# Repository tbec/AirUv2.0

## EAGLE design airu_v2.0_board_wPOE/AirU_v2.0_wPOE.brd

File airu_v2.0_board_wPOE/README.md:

# AirUv2.0 Schematic and Layout

Last Modified: …

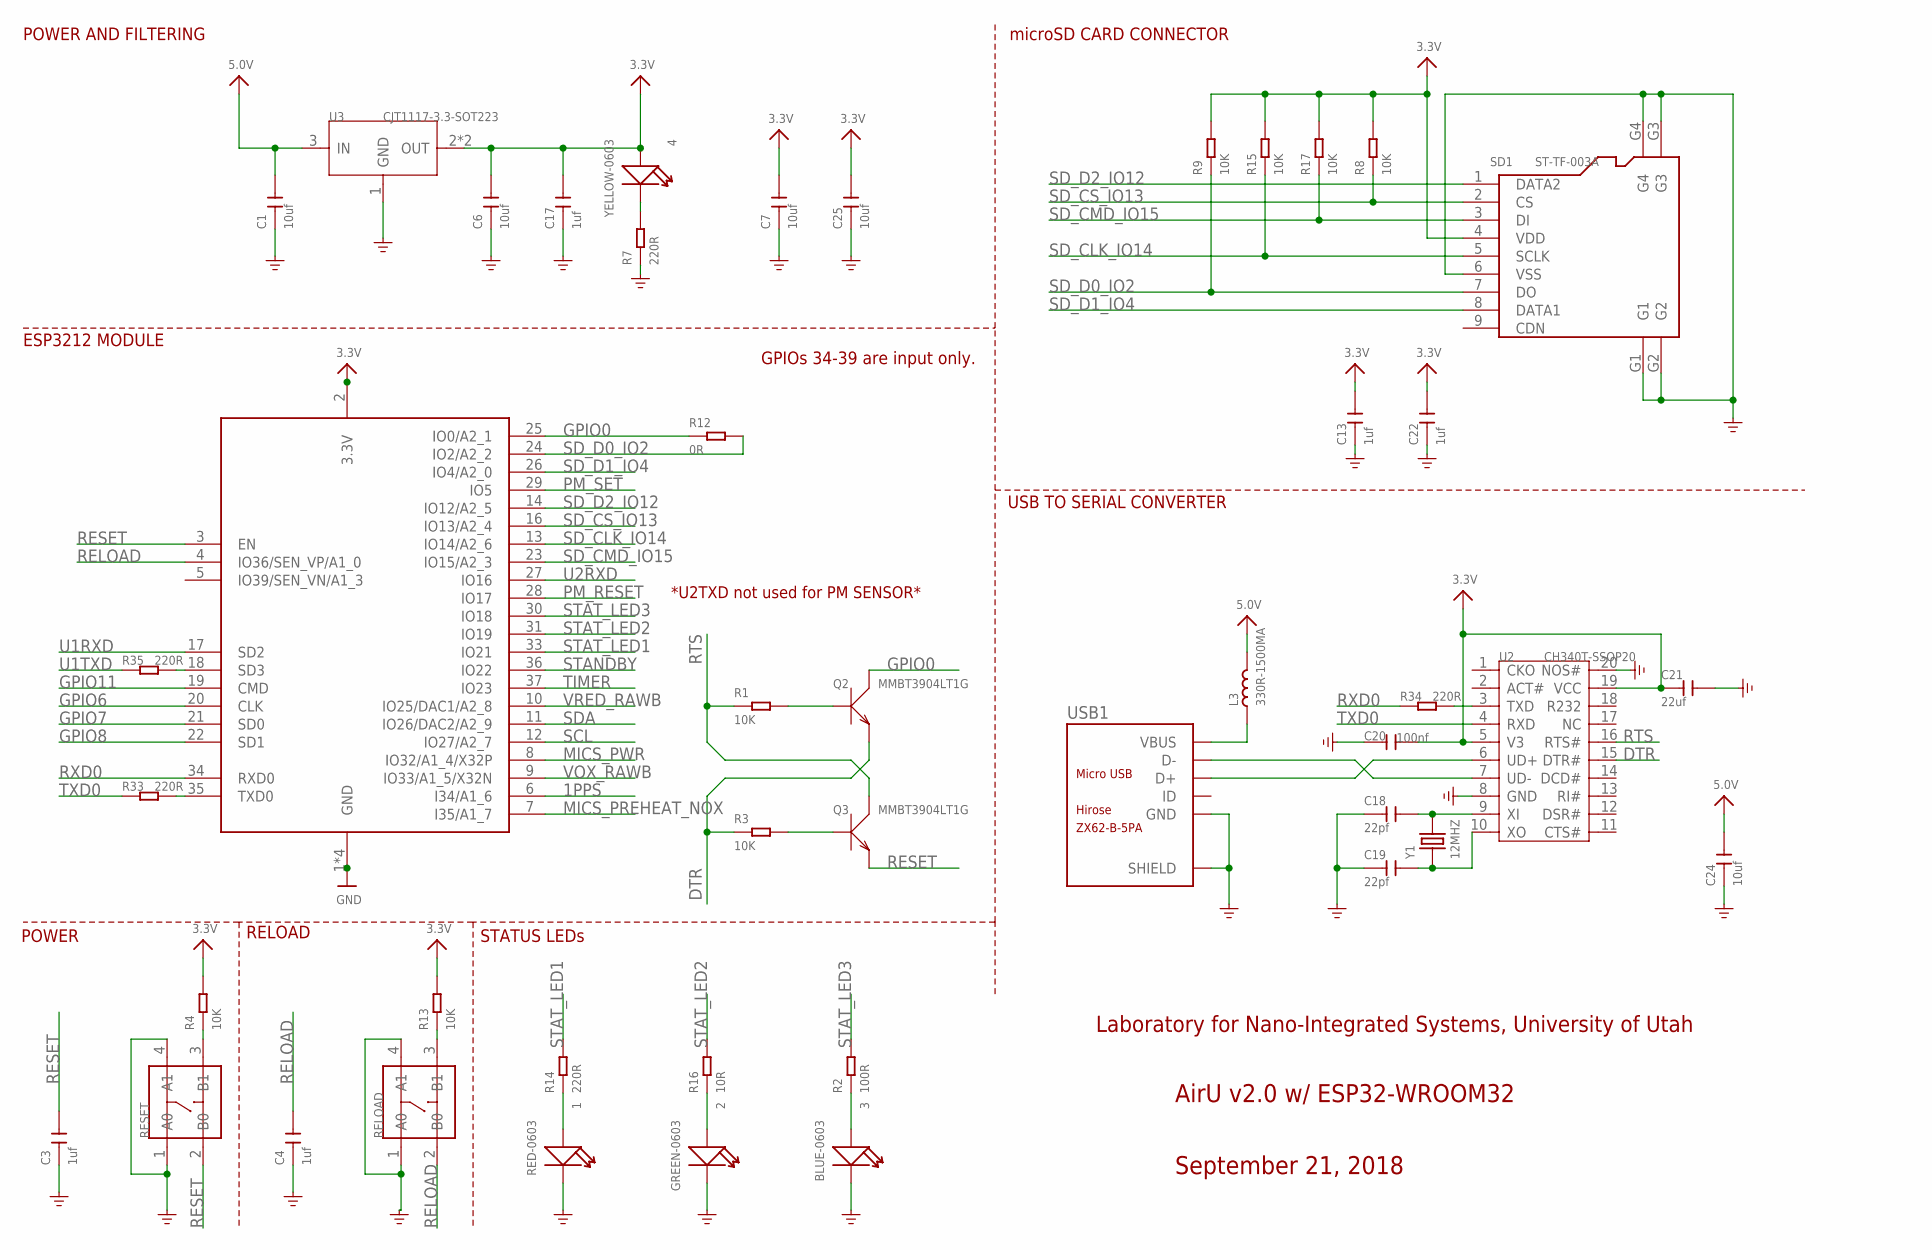
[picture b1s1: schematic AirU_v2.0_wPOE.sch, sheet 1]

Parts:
1: RED-0603; LED-0603
2: GREEN-0603; LED-0603
3: BLUE-0603; LED-0603
4: YELLOW-0603; LED-0603
C1, C6, C7, C24, C25: 10uf; C0603
C3, C4, C13, C17, C22: 1uf; C0603
C18, C19: 22pf; C0603
C20: 100nf; C0603
C21: 22uf; C0805
L3: 330R-1500MA; L0805
Q2, Q3: MMBT3904LT1G; SOT-23
R1, R3, R4, R8, R9, R13, R15, R17: 10K; R0603
R2: 100R; R0603
R7, R14, R33, R34, R35: 220R; R0603
R12: 0R; R0603
R16: 10R; R0603
RELOAD: DIP-SWITCH-TACTILE-SPST-NO/TS-1109(4P-D6.0MM)'TS-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; SW4-6.0X6.0X5.0MM
RESET: DIP-SWITCH-TACTILE-SPST-NO/TS-1109(4P-D6.0MM)'TS-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; SW4-6.0X6.0X5.0MM
SD1: ST-TF-003A; MICRO-SD9+4P-SMD-16.1X14.5X1.85MM
U2: CH340T-SSOP20; SSOP20-0.65-7.6X5.2MM
U3: CJT1117-3.3-SOT223; SOT-223
U7: ESP32_WROOM32_SKINNY; WROOM32_SKINNY
USB1: ZX62-B-5PA; MICRO-USB5+6P-SMD-0.65-AB
Y1: 12MHZ; X2-SMD-5.0X3.2X1.3MM

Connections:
1PPS: U7.6 (I34/A1_6); also elsewhere on the board
3.3V: 4.+, C6.2, C7.2, C13.2, C17.2, C20.2, C21.1, C22.2, C25.2, R4.2, R8.2, R9.2, R13.2, R15.2, R17.2, SD1.4 (VDD), U2.5 (V3), U2.19 (VCC), U3.2 (OUT), U3.TER (OUT), U7.2 (3.3V); also elsewhere on the board
5.0V: C1.2, C24.2, L3.2, U3.3 (IN); also elsewhere on the board
DTR: Q2.2 (E), R3.1, U2.15 (DTR#)
GND: 1.-, 2.-, 3.-, C1.1, C3.1, C4.1, C6.1, C7.1, C13.1, C17.1, C18.1, C19.1, C20.1, C21.2, C22.1, C24.1, C25.1, R7.1, RELOAD.1 (A0), RELOAD.4 (A1), RESET.1 (A0), RESET.4 (A1), SD1.6 (VSS), SD1.G1, SD1.G2, SD1.G3, SD1.G4, U2.8 (GND), U2.20 (NOS#), U3.1 (GND), U7.1 (GND), U7.15 (GND), U7.38 (GND), U7.P$1 (GND), USB1.5 (GND), USB1.P1 (SHIELD), USB1.P2 (SHIELD), USB1.P3_1 (SHIELD), USB1.P3_2 (SHIELD), USB1.P3_3 (SHIELD), USB1.P4_1 (SHIELD), USB1.P4_2 (SHIELD), USB1.P4_3 (SHIELD), USB1.P5 (SHIELD), USB1.P6 (SHIELD); also elsewhere on the board
GPIO0: Q2.3 (C), R12.1, U7.25 (IO0/A2_1)
GPIO6: U7.20 (CLK); also elsewhere on the board
GPIO7: U7.21 (SD0); also elsewhere on the board
GPIO8: U7.22 (SD1); also elsewhere on the board
GPIO11: U7.19 (CMD); also elsewhere on the board
MICS_PREHEAT_NOX: U7.7 (I35/A1_7); also elsewhere on the board
MICS_PWR: U7.8 (IO32/A1_4/X32P); also elsewhere on the board
unnamed: 2.+, R16.1
unnamed: 1.+, R14.1
unnamed: Q3.1 (B), R3.2
unnamed: Q2.1 (B), R1.2
unnamed: 3.+, R2.1
unnamed: 4.-, R7.2
unnamed: U2.7 (UD-), USB1.2 (D-)
unnamed: U2.6 (UD+), USB1.3 (D+)
unnamed: C18.2, U2.9 (XI), Y1.2
unnamed: C19.2, U2.10 (XO), Y1.1
unnamed: R34.2, U2.3 (TXD)
unnamed: R35.2, U7.18 (SD3)
unnamed: R33.2, U7.35 (TXD0)
unnamed: R13.1, RELOAD.3 (B1)
unnamed: R4.1, RESET.3 (B1)
PM_RESET: U7.28 (IO17); also elsewhere on the board
PM_SET: U7.29 (IO5); also elsewhere on the board
RELOAD: C4.2, RELOAD.2 (B0), U7.4 (IO36/SEN_VP/A1_0)
RESET: C3.2, Q3.2 (E), RESET.2 (B0), U7.3 (EN)
RTS: Q3.3 (C), R1.1, U2.16 (RTS#)
RXD0: R34.1, U7.34 (RXD0)
SCL: U7.12 (IO27/A2_7); also elsewhere on the board
SDA: U7.11 (IO26/DAC2/A2_9); also elsewhere on the board
SD_CLK_IO14: R15.1, SD1.5 (SCLK), U7.13 (IO14/A2_6)
SD_CMD_IO15: R17.1, SD1.3 (DI), U7.23 (IO15/A2_3)
SD_CS_IO13: R8.1, SD1.2 (CS), U7.16 (IO13/A2_4)
SD_D0_IO2: R9.1, R12.2, SD1.7 (DO), U7.24 (IO2/A2_2)
SD_D1_IO4: SD1.8 (DATA1), U7.26 (IO4/A2_0)
SD_D2_IO12: SD1.1 (DATA2), U7.14 (IO12/A2_5)
STANDBY: U7.36 (IO22); also elsewhere on the board
STAT_LED1: R14.2, U7.33 (IO21)
STAT_LED2: R16.2, U7.31 (IO19)
STAT_LED3: R2.2, U7.30 (IO18)
TIMER: U7.37 (IO23); also elsewhere on the board
TXD0: R33.1, U2.4 (RXD)
U1RXD: U7.17 (SD2); also elsewhere on the board
U1TXD: R35.1; also elsewhere on the board
U2RXD: U7.27 (IO16); also elsewhere on the board
VBUS: L3.1, USB1.1 (VBUS)
VOX_RAWB: U7.9 (IO33/A1_5/X32N); also elsewhere on the board
VRED_RAWB: U7.10 (IO25/DAC1/A2_8); also elsewhere on the board

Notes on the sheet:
POWER AND FILTERING
RELOAD
USB TO SERIAL CONVERTER
ESP3212 MODULE
POWER
microSD CARD CONNECTOR
AirU v2.0 w/ ESP32-WROOM32
September 21, 2018
STATUS LEDs
*U2TXD not used for PM SENSOR*
GPIOs 34-39 are input only.
Laboratory for Nano-Integrated Systems, University of Utah

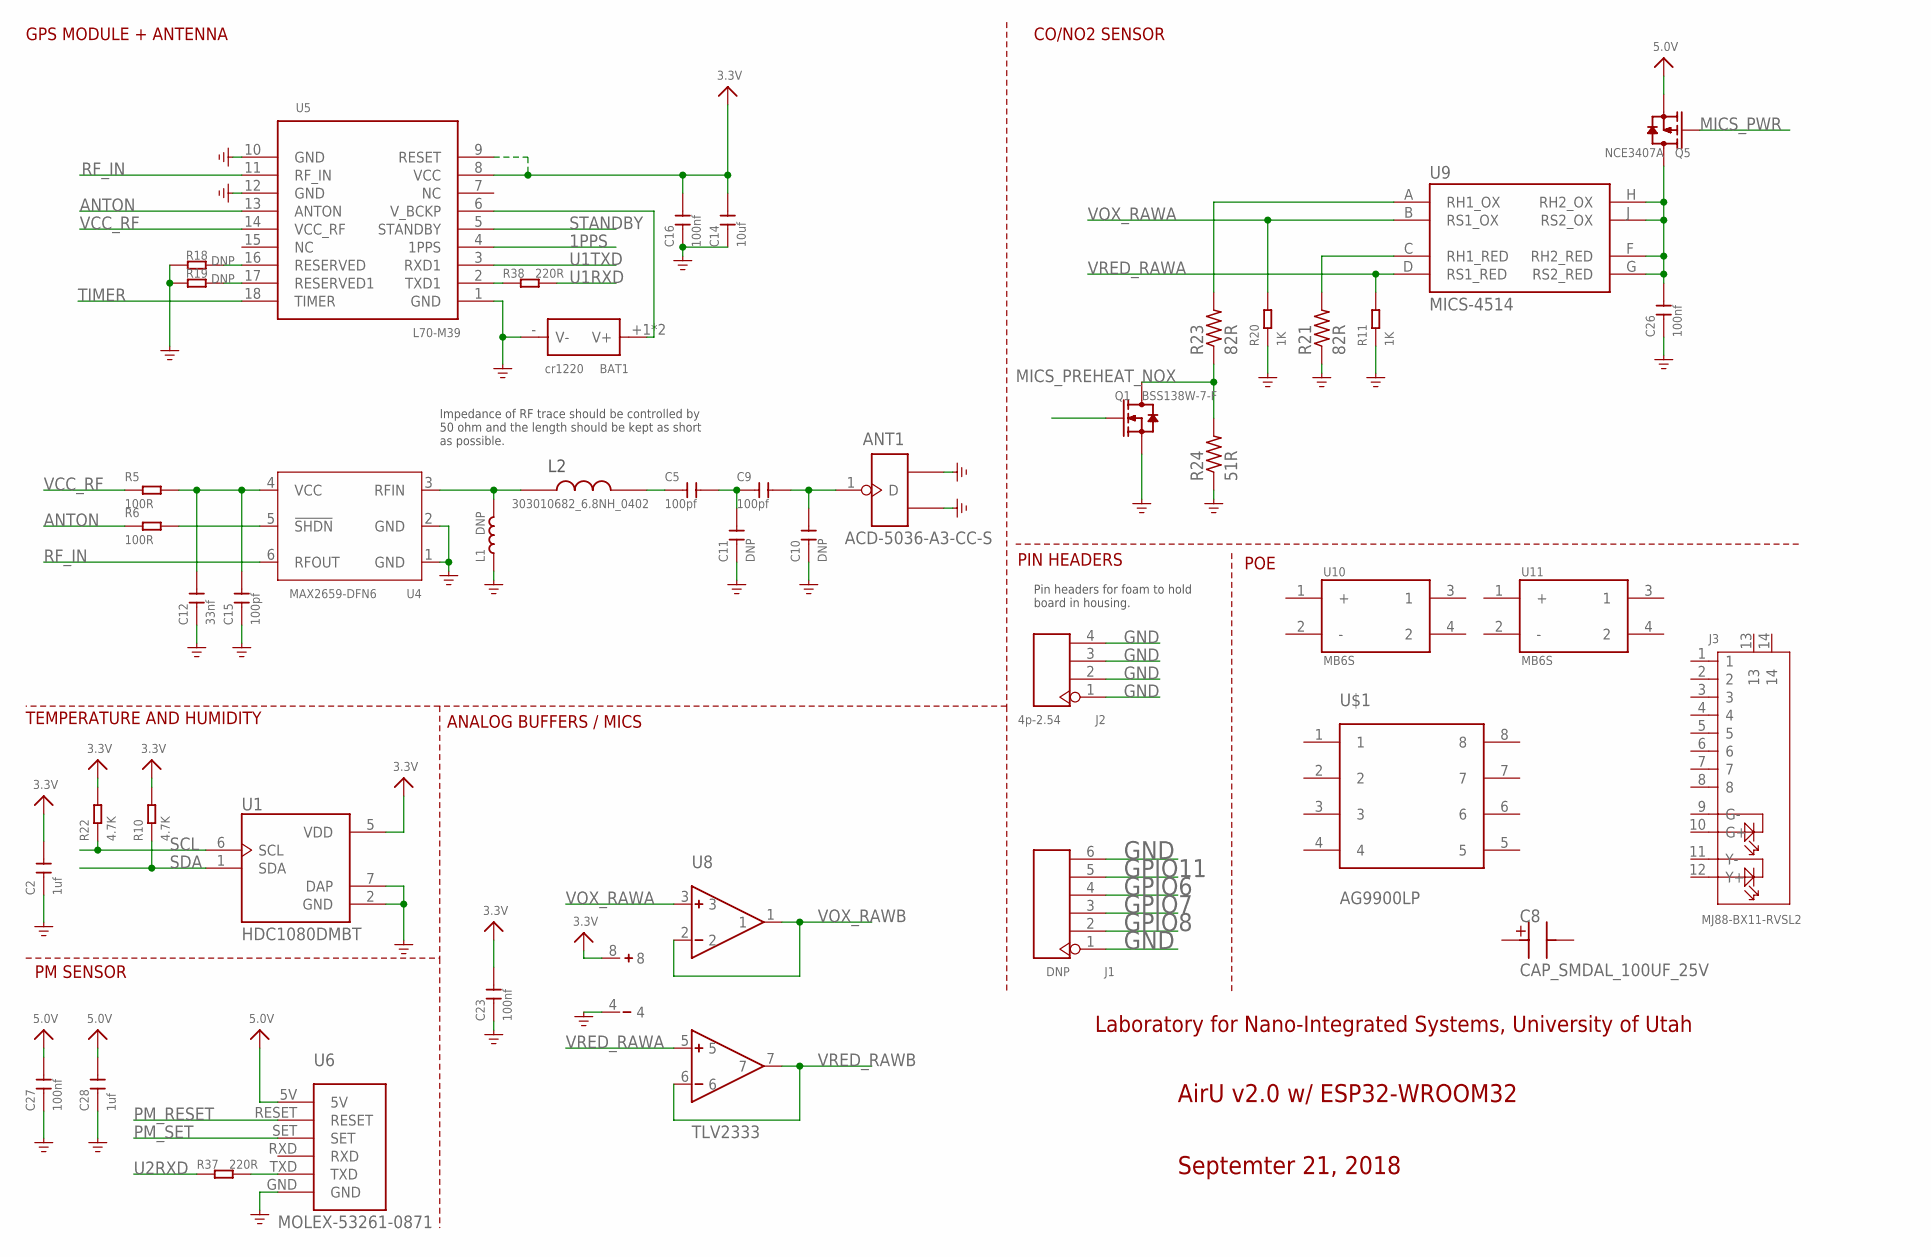
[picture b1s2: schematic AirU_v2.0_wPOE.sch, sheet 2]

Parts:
ANT1: ACD-5036-A3-CC-S; ANT3-SMD-5.2X3.7X0.7MM
BAT1: cr1220; BAT2P-13.5-CR1220
C2, C28: 1uf; C0603
C5, C9, C15: 100pf; C0603
C8: CAP_SMDAL_100UF_25V; CAP_SMD_AL_D63
C10, C11: DNP; C0603
C12: 33nf; C0603
C14: 10uf; C0603
C16, C23, C26, C27: 100nf; C0603
J1: DNP; H6-2.54
J2: 4p-2.54; H4-2.54
J3: MJ88-BX11-RVSL2; RJ45-12+2P-16.3X15.4X11.5MM-IN
L1: DNP; L0201
L2: 303010682_6.8NH_0402; L0402
Q1: BSS138W-7-F; SOT-23
Q5: NCE3407A; SOT-23
R5, R6: 100R; R0603
R10, R22: 4.7K; R0603
R11, R20: 1K; R0603
R18, R19: DNP; R0603
R21, R23: 82R; R0603
R24: 51R; R0603
R37, R38: 220R; R0603
U1: HDC1080DMBT; SON100P300X300X80-7N
U4: MAX2659-DFN6; DFN6-0.5-1.5X1.2X0.72MM
U5: L70-M39; LGA18-1.1-9.7X10.1X2.5MM
U6: MOLEX-53261-0871
U8: TLV2333
U9: MICS-4514; MICS_10-SMD
U10, U11: MB6S; SOIC245P670X270-4N
U$1: AG9900LP

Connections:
1PPS: U5.4 (1PPS); also elsewhere on the board
3.3V: C2.2, C14.2, C16.2, C23.2, R10.2, R22.2, U1.5 (VDD), U5.8 (VCC), U5.9 (RESET), U8.8; also elsewhere on the board
5.0V: C27.2, C28.2, Q5.2 (S), U6.5V; also elsewhere on the board
ANTON: R6.1, U5.13 (ANTON)
GND: ANT1.2 (GND1), ANT1.3 (GND2), BAT1.- (V-), C2.1, C10.1, C11.1, C12.1, C14.1, C15.1, C16.1, C23.1, C26.1, C27.1, C28.1, J1.1, J1.6, J2.1, J2.2, J2.3, J2.4, L1.1, Q1.2 (S), R11.1, R18.1, R19.1, R20.1, R21.1, R24.1, U1.2 (GND), U1.7 (DAP), U4.1 (GND), U4.2 (GND), U5.1 (GND), U5.10 (GND), U5.12 (GND), U6.GND, U8.4; also elsewhere on the board
GPIO6: J1.4; also elsewhere on the board
GPIO7: J1.3; also elsewhere on the board
GPIO8: J1.2; also elsewhere on the board
GPIO11: J1.5; also elsewhere on the board
MICS_PREHEAT_NOX: Q1.1 (G); also elsewhere on the board
MICS_PWR: Q5.1 (G); also elsewhere on the board
unnamed: R21.2, U9.C (RH1_RED)
unnamed: C5.2, C9.1, C11.2
unnamed: ANT1.1 (D), C9.2, C10.2
unnamed: L1.2, L2.P$1, U4.3 (RFIN)
unnamed: R23.2, U9.A (RH1_OX)
unnamed: C5.1, L2.P$2
unnamed: R6.2, U4.5 (!SHDN)
unnamed: C12.2, C15.2, R5.2, U4.4 (VCC)
unnamed: R18.2, U5.16 (RESERVED)
unnamed: R19.2, U5.17 (RESERVED1)
unnamed: BAT1.+1 (V+), BAT1.+2 (V+), U5.6 (V_BCKP)
unnamed: R38.1, U5.2 (TXD1)
unnamed: Q1.3 (D), R23.1, R24.2
unnamed: C26.2, Q5.3 (D), U9.F (RH2_RED), U9.G (RS2_RED), U9.H (RH2_OX), U9.J (RS2_OX)
unnamed: R37.2, U6.TXD
PM_RESET: U6.RESET; also elsewhere on the board
PM_SET: U6.SET; also elsewhere on the board
RF_IN: U4.6 (RFOUT), U5.11 (RF_IN)
SCL: R22.1, U1.6 (SCL); also elsewhere on the board
SDA: R10.1, U1.1 (SDA); also elsewhere on the board
STANDBY: U5.5 (STANDBY); also elsewhere on the board
TIMER: U5.18 (TIMER); also elsewhere on the board
U1RXD: R38.2; also elsewhere on the board
U1TXD: U5.3 (RXD1); also elsewhere on the board
U2RXD: R37.1; also elsewhere on the board
VCC_RF: R5.1, U5.14 (VCC_RF)
VOX_RAWA: R20.2, U8.3, U9.B (RS1_OX)
VOX_RAWB: U8.1, U8.2; also elsewhere on the board
VRED_RAWA: R11.2, U8.5, U9.D (RS1_RED)
VRED_RAWB: U8.6, U8.7; also elsewhere on the board

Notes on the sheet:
PM SENSOR
Impedance of RF trace should be controlled by 50 ohm and the length should be kept as short as possible.
TEMPERATURE AND HUMIDITY
GPS MODULE + ANTENNA
CO/NO2 SENSOR
AirU v2.0 w/ ESP32-WROOM32
Septemter 21, 2018
ANALOG BUFFERS / MICS
PIN HEADERS
Laboratory for Nano-Integrated Systems, University of Utah
Pin headers for foam to hold board in housing.
POE

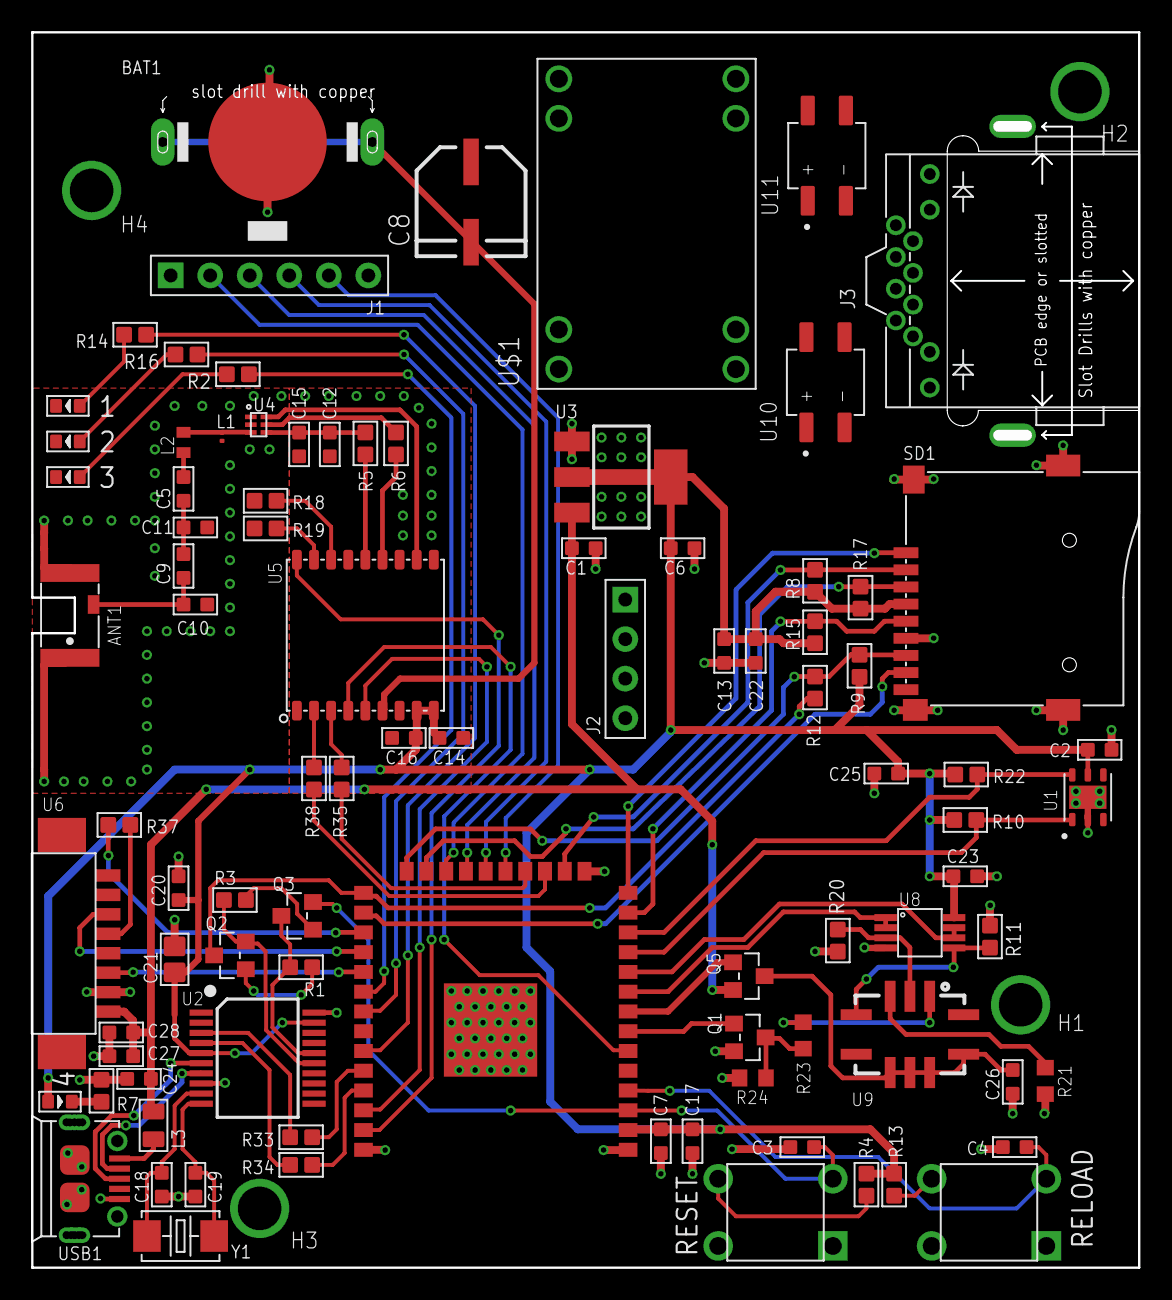
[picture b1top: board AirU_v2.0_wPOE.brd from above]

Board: 2 copper layers, 70.6 x 78.8 mm, 90 parts (0 on the bottom side), 73 nets.

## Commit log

2018-10-03 add v2 board eagle files
2018-10-04 add bom file for v2.0 board
2018-10-04 add my demo modules
2018-10-04 add readme to board diirectory
2018-10-04 update readme for eagle files
2018-10-04 add modules readme
2018-10-04 add v2.0 board dimensions
2018-10-04 add anternate v2.0 boards
2018-10-04 add firmware project setup
2018-10-04 rename dir for board
2018-10-04 try to rename dir
2018-10-04 add eagle files for v2.0 board
2018-10-04 add readmes
2018-10-06 fix path issue
2018-10-06 add pm_if folder
2018-10-06 remove unused folder
2018-10-06 put pm module into project
2018-10-06 move header files from .h to src file for pm
2018-10-07 start GPS module

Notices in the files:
parts and their libraries:
microbuilder: This work is placed in the public domain, and may be freely used for commercial and non-commercial work with the following conditions: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
